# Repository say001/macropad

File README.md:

# macropad
A 8 key macropad with a rotary ecnoder. Uses KMK firmware. 

# cad
Has a top cover and the bottom case for the circuit board and pieces.
Made with Fusion.

# pcb
Pictures of the schematic and the pcb. (made in kicad)

# materials
- 1x Seeed XIAO RP2040
- 8x Through-hole 1N4148 Diodes
- 1x EC11 Rotary encoders
- 8x Blank DSA keycaps
- 8x Cherry MX Switches
- 6x SK6812 MINI-E LEDs

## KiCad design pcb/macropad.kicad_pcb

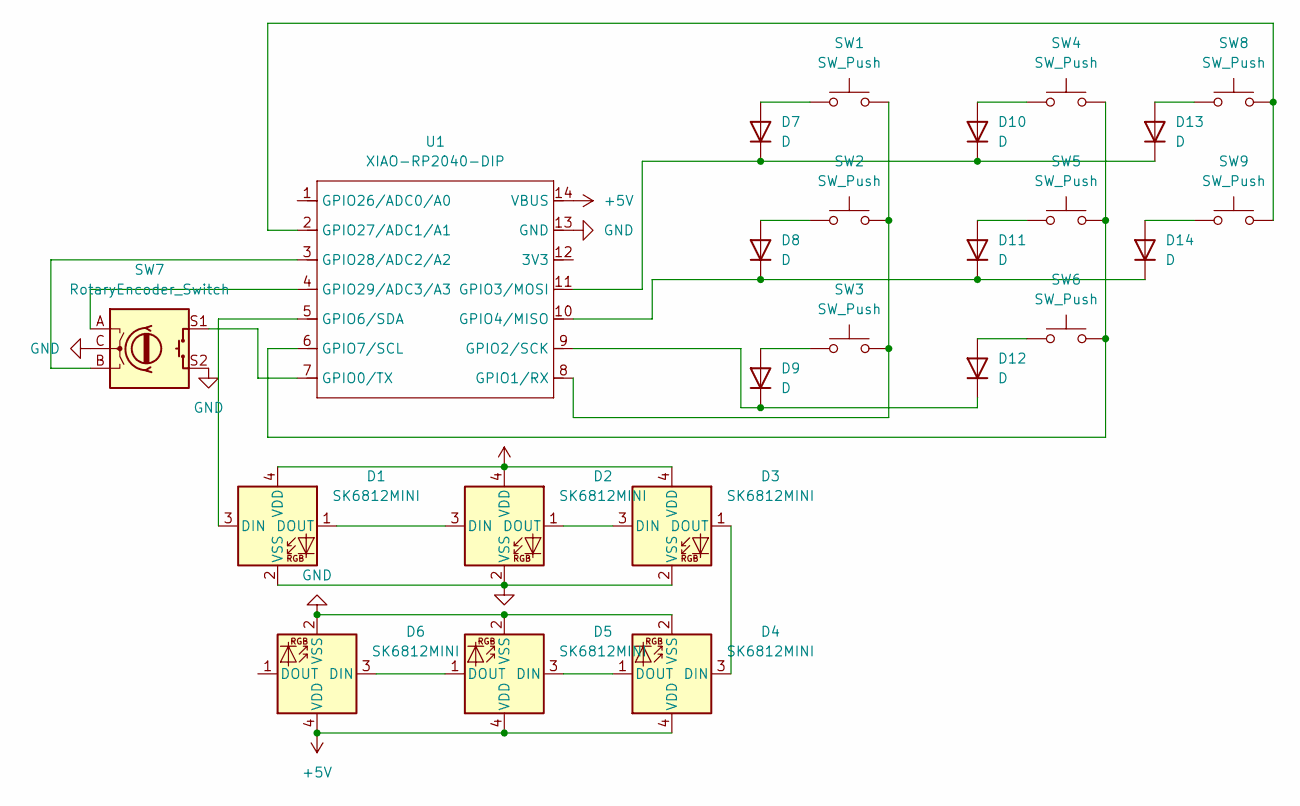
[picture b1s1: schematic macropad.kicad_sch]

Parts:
D1, D2, D3, D4, D5, D6: SK6812MINI; LED_SK6812MINI_PLCC4_3.5x3.5mm_P1.75mm
D7, D8, D9, D10, D11, D12, D13, D14: D; D_DO-35_SOD27_P7.62mm_Horizontal
SW1, SW2, SW3, SW4, SW5, SW6, SW8, SW9: SW_Push; SW_Cherry_MX_1.00u_PCB
SW7: RotaryEncoder_Switch; RotaryEncoder_Alps_EC11E-Switch_Vertical_H20mm_CircularMoun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
U1: XIAO-RP2040-DIP

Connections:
+5V: D1.4 (VDD), D2.4 (VDD), D3.4 (VDD), D4.4 (VDD), D5.4 (VDD), D6.4 (VDD), U1.14 (VBUS)
GND: D1.2 (VSS), D2.2 (VSS), D3.2 (VSS), D4.2 (VSS), D5.2 (VSS), D6.2 (VSS), SW7.C, SW7.S2, U1.13 (GND)
unnamed: D1.3 (DIN), U1.5 (GPIO6/SDA)
unnamed: D1.1 (DOUT), D2.3 (DIN)
unnamed: D2.1 (DOUT), D3.3 (DIN)
unnamed: D3.1 (DOUT), D4.3 (DIN)
unnamed: D4.1 (DOUT), D5.3 (DIN)
unnamed: D5.1 (DOUT), D6.3 (DIN)
unnamed: D7.2 (A), SW1.1
unnamed: D8.2 (A), SW2.1
unnamed: D9.2 (A), SW3.1
unnamed: D10.2 (A), SW4.1
unnamed: D7.1 (K), D10.1 (K), D13.1 (K), U1.11 (GPIO3/MOSI)
unnamed: D11.2 (A), SW5.1
unnamed: D8.1 (K), D11.1 (K), D14.1 (K), U1.10 (GPIO4/MISO)
unnamed: D12.2 (A), SW6.1
unnamed: D9.1 (K), D12.1 (K), U1.9 (GPIO2/SCK)
unnamed: D13.2 (A), SW8.1
unnamed: D14.2 (A), SW9.1
unnamed: SW7.S1, U1.7 (GPIO0/TX)
unnamed: SW1.2, SW2.2, SW3.2, U1.8 (GPIO1/RX)
unnamed: SW4.2, SW5.2, SW6.2, U1.6 (GPIO7/SCL)
unnamed: SW8.2, SW9.2, U1.2 (GPIO27/ADC1/A1)
unnamed: SW7.B, U1.3 (GPIO28/ADC2/A2)
unnamed: SW7.A, U1.4 (GPIO29/ADC3/A3)

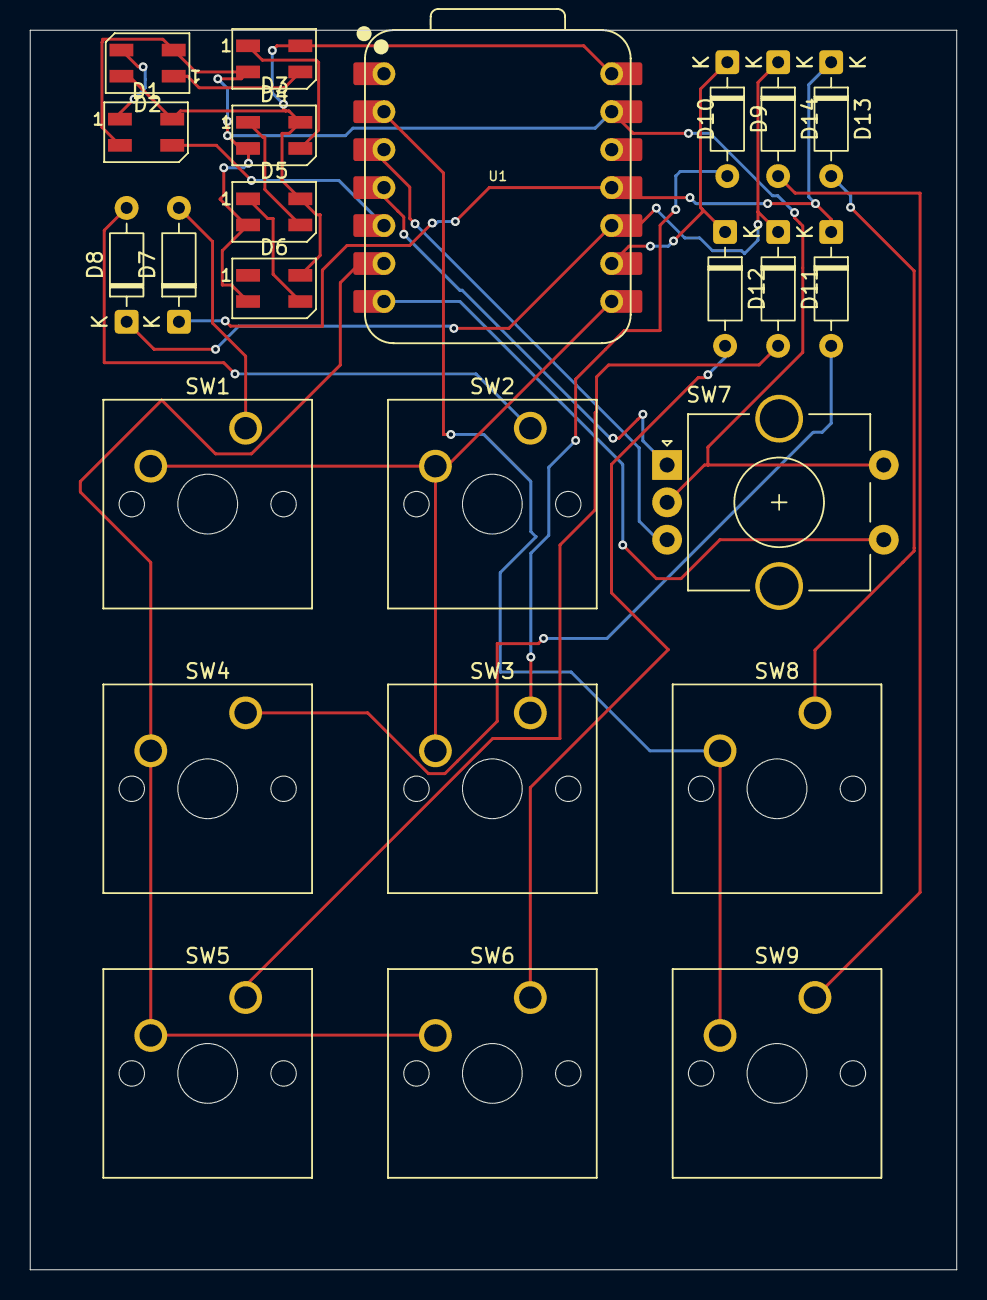
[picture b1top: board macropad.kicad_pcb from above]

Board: 2 copper layers, 62.0 x 82.9 mm, 24 parts (0 on the bottom side), 25 nets.

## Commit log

2025-08-01 added files
2025-08-01 added cad as two separate files in cad folder
2025-08-17 fixed cad
2025-08-17 added gerber files as zip
2025-08-26 compressed gerber files to zip
